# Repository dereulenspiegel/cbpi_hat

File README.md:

# CraftBeerPi Hat
This is a Raspberry Pi hat meant for use with [CraftBeerPi](https://github.com/craftbeerpi/craftbeerpi4).
It's created with [EasyEDA](https://easyeda.com/) and optimized for production via 
[JLCPCB](https://jlcpcb.com/).

This project is [certified](https://certification.oshwa.org/de000132.html) as open source
hardware by the [OSHWA](https://www.oshwa.org/) under the UID DE000132.

## Development

Currently this project is designed with [EasyEDA](https://easyeda.com/). You can find
all necessary files in the folder `easyeda`. When modifying this project please
respect the CERN-OHL-S license used in this project.

## Features

* Slots for up to 5 MAX31865 modules for PT100/PT1000 measurements
* 7 digital outputs with up to 1 amp of output power
* All 7 outputs have flyback diodes to drive inductive loads like solenoids
* All 7 outputs have resettable fuses for extra protection
* RTC so the Raspberry Pi doesn't loose its time in offline installations
* QWIIC connector to hookup additional sensors and actors following the 
  SparkFun QWIIC specification
* OneWire connection for additional sensors
* Can operate on 12-24V, digital outputs operate directly on input voltage
* Reverse voltage protection (but please be still be careful)

Please note that the digital outputs are inverted in logic due to the push pull stage, but
CraftBeerPi supports inverting GPIO actors.

# Polarity of connectors!!!

This board is powered by 12-24V and provides some reverse polarity protection. But still
please be careful when wiring up the board. Looking at the front of a connector the left
side of a connector is always the negative side and the right side of a connector is always
the positive side!

PCB:

Schematic:

## PIN configuration

### Digital outputs

Digital outputs are counted starting on the most left. Outputs 2,3 and 7 are marked on the edge of
the PCBs upper layer. On the bottom layer every output is numbered and the polarity marked. On the
upper layer polarity markings are only next to the outer most ports on each side. But polarity is
always left side negative, right side positive.

| Output # | GPIO |
|----------|------|
| 1 | 25 |
| 2 |  8 |
| 3 |  7 |
| 4 | 12 |
| 5 | 16 |
| 6 | 20 |
| 7 | 21 |

### MAX31865 modules

The MAX31865 modules are connected via SPI and each have a different CS-Pin. Modules
1,2,3,5 are mounted with the upper side facing left (towards the power connector and the SD-card
slot of the Raspberry Pi). Module 5 is flipped 180°. Every module connector has the first two and
last two pins marked with the same markings as the module to ensure the correct orientation.

| Modules # | GPIO CS |
|-----------|---------|
| 1 | 17 |
| 2 | 27 |
| 3 | 22 |
| 4 |  5 |
| 5 |  6 |

### OneWire

The OneWire data line is connected to `GPIO 4`. The pins on the connector are marked behind the connector
on the top side of the PCB. They are, from left to right `VCC` - `DAT` - `GND`. A 4.7k pull up is
already provided on the board.
To enable OneWire support on a Raspberry Pi you need to add
```
dtoverlay=w1-gpio,gpiopin=4
```
to your config.txt

### RealTime Clock

The RTC (DS3231) is connected via I2C and should be usable by adding
```
dtparam=i2c_arm=on
dtoverlay=i2c-rtc,ds3231
```
to your config.txt

## Known Caveats

### Revision 1.0

* On revision 1.0 outputs 2 and 3 are mapped to chip enable pins of SPI0. Users need to disable CE pins on SPI0
* On revision 1.0 outputs are not in the desired off state during and directly after boot

To solve these issues the Raspberry Pi can be configured via config.txt.
With adding `dtoverlay=spi0-0cs` to the config.txt you can disable the hardware CE pins for SPI 0, freeing up GPIO 7 and 8
making Output 2 and 3 freely usabel.
With `gpio=25,7,8,12,16,20,21=op,dh` in the config.txt we set all pins controlling powered outputs to output and pull them high
as early as possible to disable the outputs. During power on there might be less than a second where the outputs might be enabled.

## Full config.txt additions for this board

```
# Enable SPI
dtparam=spi=on
# Enable 1-Wire
dtoverlay=w1-gpio,gpiopin=4
# Enable RTC
dtparam=i2c_arm=on
dtoverlay=i2c-rtc,ds3231
# Disable SPI0 CE pins
dtoverlay=spi0-0cs
# Disable outputs on boot
gpio=25,7,8,12,16,20,21=op,dh
```

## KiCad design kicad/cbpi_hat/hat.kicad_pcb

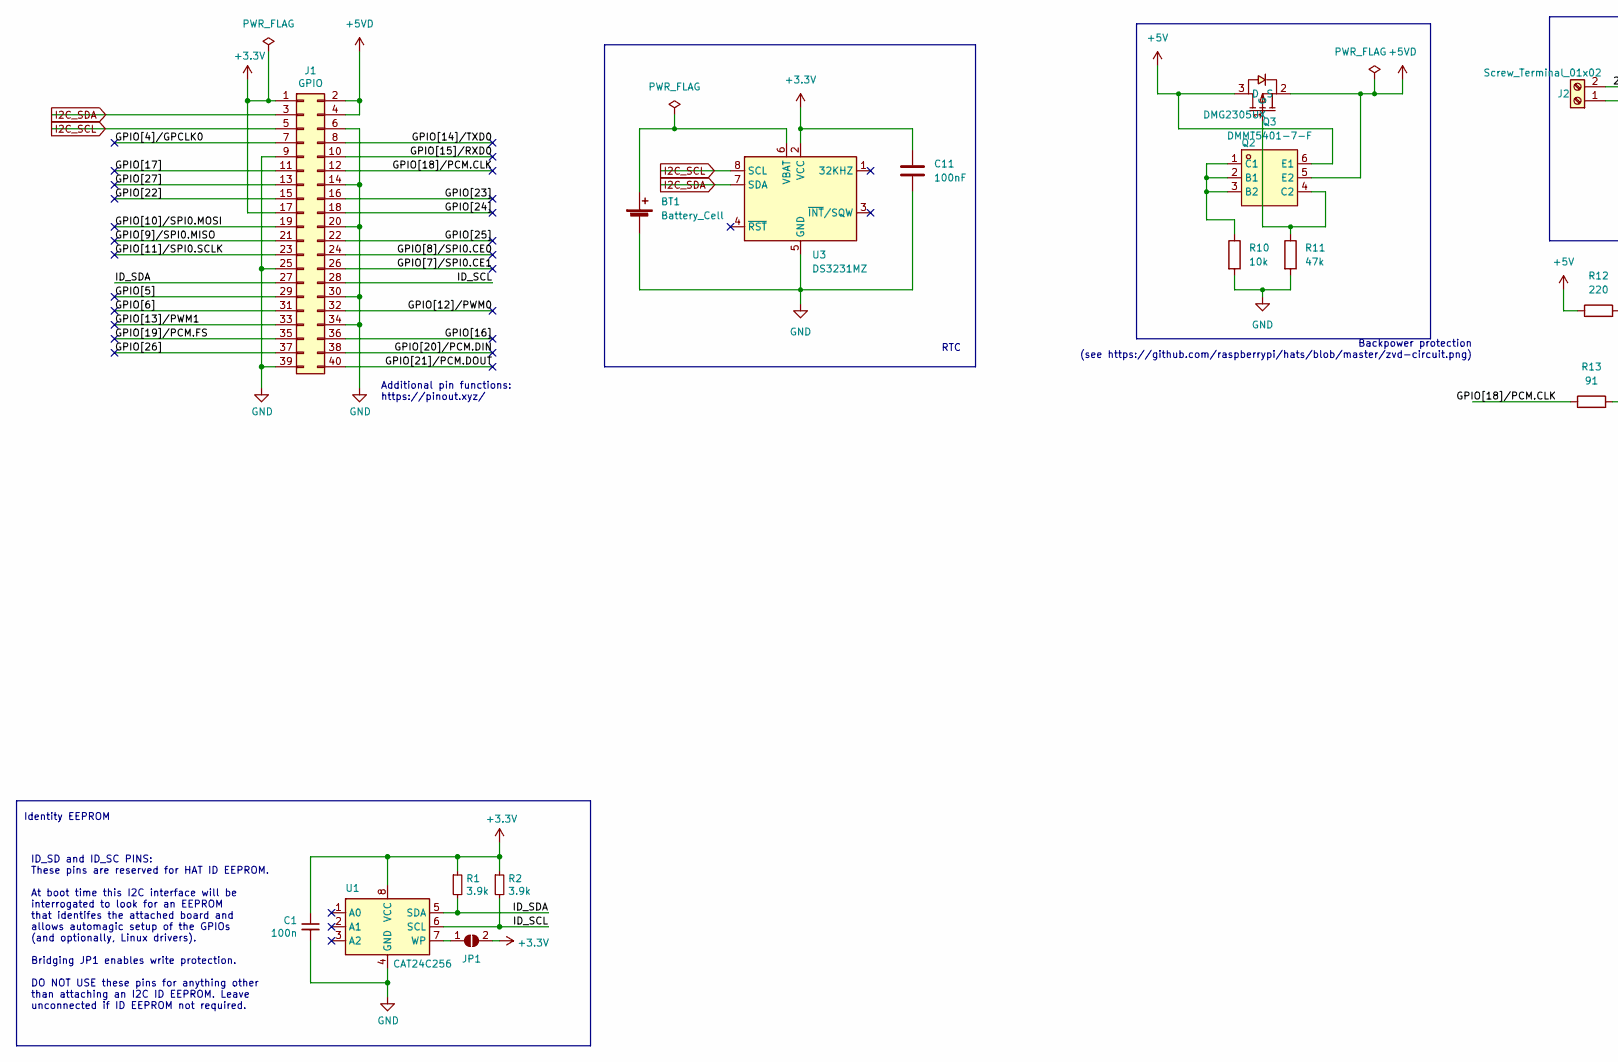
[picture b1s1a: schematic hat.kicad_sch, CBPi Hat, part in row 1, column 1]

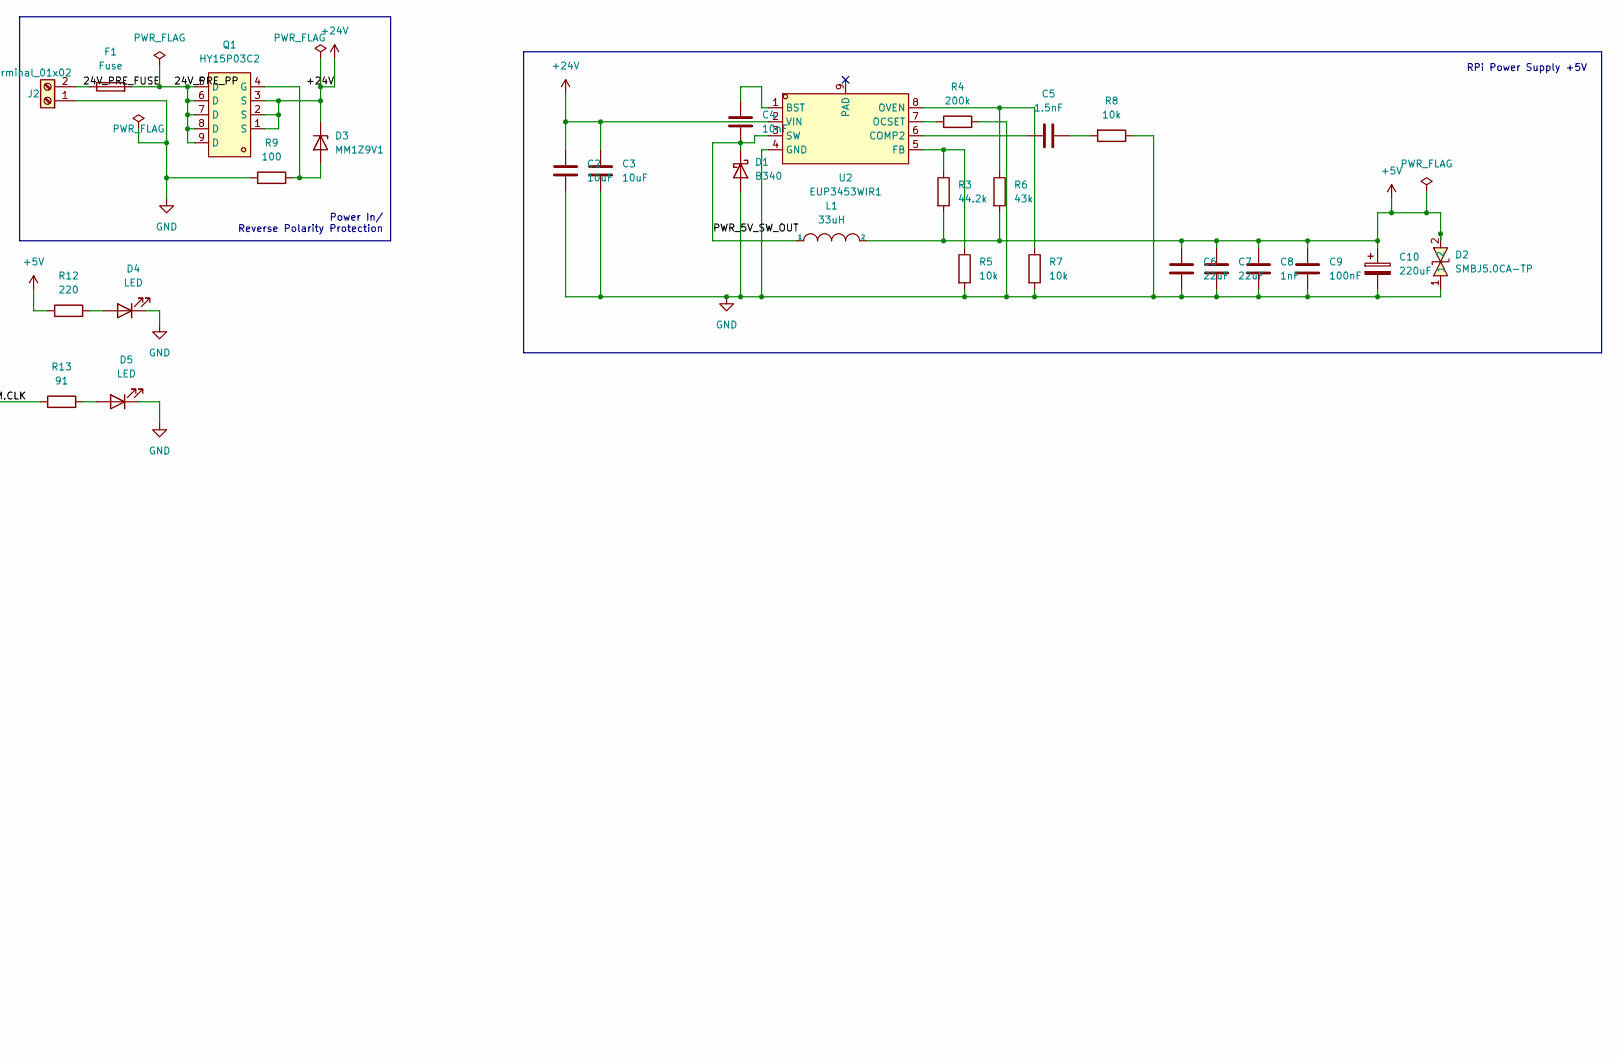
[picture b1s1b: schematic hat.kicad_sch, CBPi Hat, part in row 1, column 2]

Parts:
BT1: Battery_Cell; BAT-TH_CR2032-BS-5-1
C1: 100n; C_0603_1608Metric
C2, C3: 10uF; C_1206_3216Metric
C4: 10nF; C_0603_1608Metric
C5: 1.5nF; C_0603_1608Metric
C6, C7: 22uF; C_0805_2012Metric
C8: 1nF; C_0603_1608Metric
C9, C11: 100nF; C_0603_1608Metric
C10: 220uF; C_Elec_6.3x5.4
D1: B340; D_SMA
D2: SMBJ5.0CA-TP; SMB_L4.6-W3.6-LS5.3-BI; LCSC Part C78757
D3: MM1Z9V1; D_SOD-123
D4, D5: LED; LED_0603_1608Metric
F1: Fuse; Fuse_Blade_ATO_directSolder
J1: GPIO; PinSocket_2x20_P2.54mm_Vertical
J2: Screw_Terminal_01x02; TerminalBlock_Altech_AK300-2_P5.00mm
JP1: ID_WP; SolderJumper-2_P1.3mm_Open_RoundedPad1.0x1.5mm
L1: 33uH; IND-SMD_L11.5-W10.0
Q1: HY15P03C2; DFN-8_L5.9-W5.2-P1.27-LS6.2-BL; LCSC Part C123687
Q2: DMG2305UX; SOT-23-3_L2.9-W1.3-P0.95-LS2.4-BR-1; LCSC Part C2940629
Q3: DMMT5401-7-F; SOT-23-6_L2.9-W1.6-P0.95-LS2.8-BR; LCSC Part C154733
R1, R2: 3.9k; R_0402_1005Metric
R3: 44.2k; R_0402_1005Metric
R4: 200k; R_0402_1005Metric
R5, R7, R8: 10k; R_0603_1608Metric
R6: 43k; R_0603_1608Metric
R9: 100; R_0402_1005Metric
R10: 10k; R_0402_1005Metric
R11: 47k; R_0402_1005Metric
R12: 220; R_0402_1005Metric
R13: 91; R_0402_1005Metric
U1: CAT24C256; SOIC-8-1EP_3.9x4.9mm_P1.27mm_EP2.29x3mm
U2: EUP3453WIR1; SOIC-8_L4.9-W3.9-P1.27-LS6.0-BL-EP3.1; LCSC Part C311687
U3: DS3231MZ; SOIC-8_3.9x4.9mm_P1.27mm

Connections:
+3.3V: C1.1, C11.1, J1.1, J1.17, JP1.2 (B), R1.1, R2.1, U1.8 (VCC), U3.2 (VCC)
+5V: C6.1, C7.1, C8.1, C9.1, C10.1, D2.2, L1.2, Q2.3 (D), Q3.6 (E1), R3.2, R6.2, R12.1
+5VD: J1.2, J1.4, Q2.2 (S), Q3.5 (E2)
+24V: C2.1, C3.1, D3.1 (K), Q1.1 (S), Q1.2 (S), Q1.3 (S), U2.2 (VIN)
/24V_PRE_FUSE: F1.1, J2.2
/24V_PRE_PP: F1.2, Q1.5 (D), Q1.6 (D), Q1.7 (D), Q1.8 (D), Q1.9 (D)
/GPIO[4]/GPCLK0: J1.7
/GPIO[5]: J1.29
/GPIO[6]: J1.31
/GPIO[7]/SPI0.CE1: J1.26
/GPIO[8]/SPI0.CE0: J1.24
/GPIO[9]/SPI0.MISO: J1.21
/GPIO[10]/SPI0.MOSI: J1.19
/GPIO[11]/SPI0.SCLK: J1.23
/GPIO[12]/PWM0: J1.32
/GPIO[13]/PWM1: J1.33
/GPIO[14]/TXD0: J1.8
/GPIO[15]/RXD0: J1.10
/GPIO[16]: J1.36
/GPIO[17]: J1.11
/GPIO[18]/PCM.CLK: J1.12, R13.1
/GPIO[19]/PCM.FS: J1.35
/GPIO[20]/PCM.DIN: J1.38
/GPIO[21]/PCM.DOUT: J1.40
/GPIO[22]: J1.15
/GPIO[23]: J1.16
/GPIO[24]: J1.18
/GPIO[25]: J1.22
/GPIO[26]: J1.37
/GPIO[27]: J1.13
/ID_SCL: J1.28, R2.2, U1.6 (SCL)
/ID_SDA: J1.27, R1.2, U1.5 (SDA)
/PWR_5V_SW_OUT: C4.2, D1.1 (K), L1.1, U2.3 (SW)
GND: BT1.2 (-), C1.2, C2.2, C3.2, C6.2, C7.2, C8.2, C9.2, C10.2, C11.2, D1.2 (A), D2.1, D4.1 (K), D5.1 (K), J1.6, J1.9, J1.14, J1.20, J1.25, J1.30, J1.34, J1.39, J2.1, R4.2, R5.2, R7.2, R8.1, R9.1, R10.2, R11.2, U1.4 (GND), U2.4 (GND), U3.5 (GND)
I2C_SCL: J1.5, U3.8 (SCL)
I2C_SDA: J1.3, U3.7 (SDA)
unnamed: BT1.1 (+), U3.6 (VBAT)
unnamed: C4.1, U2.1 (BST)
unnamed: C5.1, U2.6 (COMP2)
unnamed: C5.2, R8.2
unnamed: D3.2 (A), Q1.4 (G), R9.2
unnamed: D4.2 (A), R12.2
unnamed: D5.2 (A), R13.2
unnamed: JP1.1 (A), U1.7 (WP)
unnamed: Q2.1 (G), Q3.4 (C2), R11.1
unnamed: Q3.1 (C1), Q3.2 (B1), Q3.3 (B2), R10.1
unnamed: R3.1, R5.1, U2.5 (FB)
unnamed: R4.1, U2.7 (OCSET)
unnamed: R6.1, R7.1, U2.8 (OVEN)

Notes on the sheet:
Additional pin functions: https://pinout.xyz/
Identity EEPROM
ID_SD and ID_SC PINS: These pins are reserved for HAT ID EEPROM. At boot time this I2C interface will be interrogated to look for an EEPROM that identifes the attached board and allows automagic setup of the GPIOs (and optionally, Linux drivers). Bridging JP1 enables write protection. DO NOT USE th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
RTC
Backpower protection (see https://github.com/raspberrypi/hats/blob/master/zvd-circuit.png)
RPi Power Supply +5V
Power In/ Reverse Polarity Protection

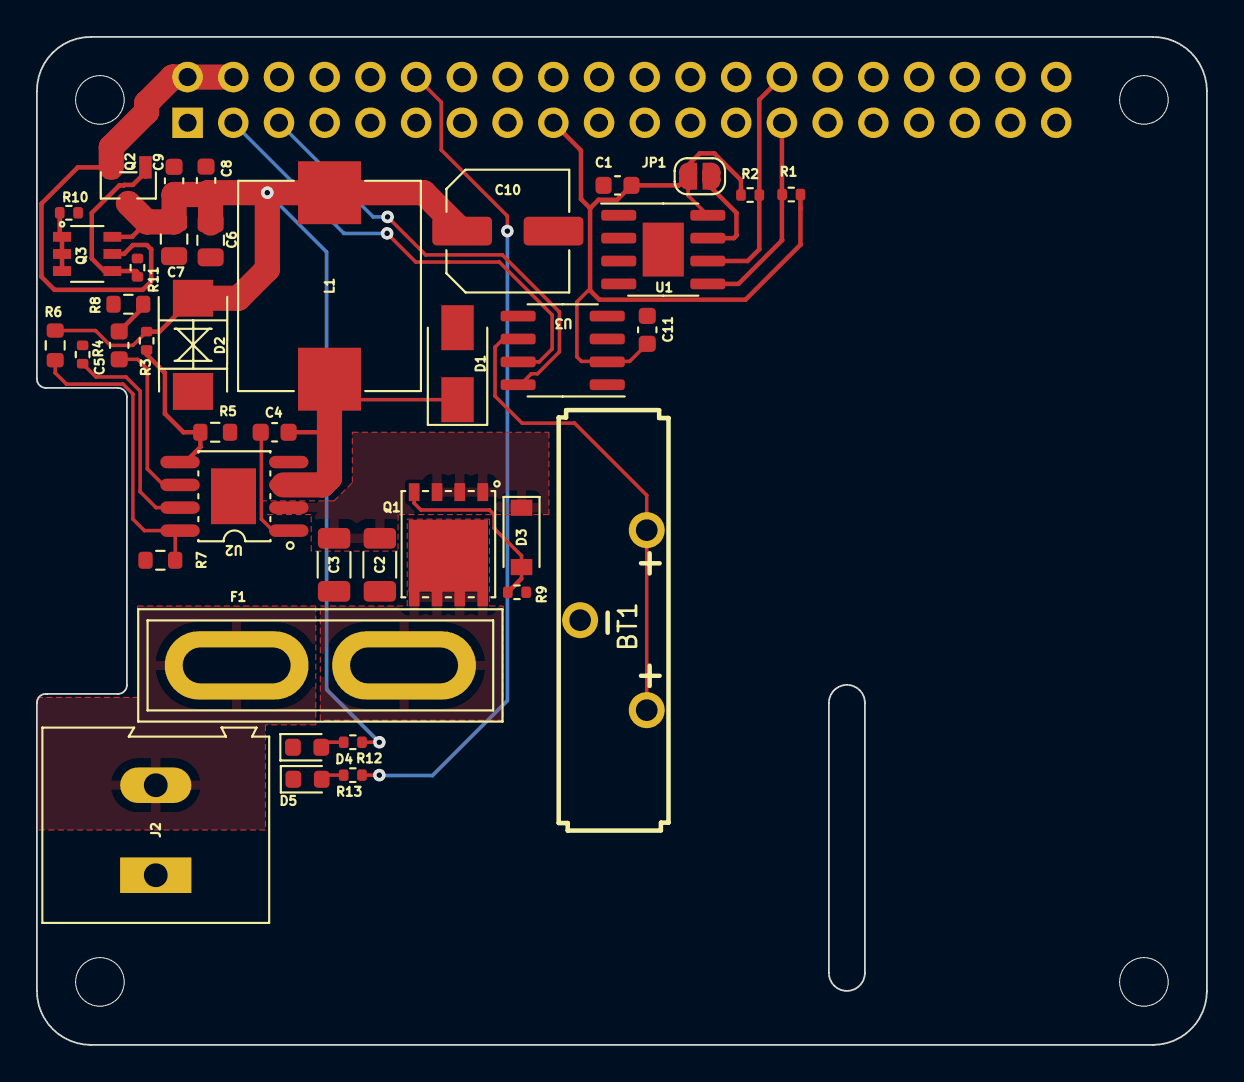
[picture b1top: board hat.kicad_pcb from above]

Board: 2 copper layers, 65.0 x 56.0 mm, 45 parts (1 on the bottom side), 26 nets.

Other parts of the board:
MH1, MH2, MH3, MH4: MountingHole_2.7mm_M2.5

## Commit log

2023-01-02 “root”
2023-01-02 Added image of schematic
2023-01-02 Added exports of production files
2023-01-02 Added pin documentation
2023-01-03 minor upgrades, mostly regarding text and documentation on the board. Improved resistors on MOSFET gates, so they don't form an unnecessary voltage divider
2023-01-03 Updated exported pictures after board changes
2023-01-03 Updated EasyEDA exports after board changes
2023-01-09 Rather large change on the PCB introducing fuses on each output and a push pull schematic for more protection of the raspberry pi as well as pull up resistors to have a defined off state for every ou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
2023-01-10 Board has now better protection in the 5V supply for the Raspberry Pi and a few optimizations and corrections in the silscreen layers and part placement
2023-01-10 Added LTSpice circuit of the digital output to simulate and verify its behavior
2023-01-10 Added note to warn users, that the digital ouputs are inverted in logic
2023-01-11 Added power indicator LED to 5V rail and further optimized a few parts placements
2023-01-11 Accidentally pushed the wrong image image as pcb image
2023-01-11 Again a few minor changes in parts placement. Mostly to optimize readability of upper silkscreen
2023-01-12 Optimized parts placement further and added reverse polarity protection, which hopefully works
2023-01-12 Fixed typos in README
2023-01-12 Added reverse volatege protection as a feature
2023-01-12 Optimized parts placement for better ground planes, as we will pump up to 10 amps through this board
2023-01-12 Fixed typo
2023-01-13 More optimization on pcb traces running power, to minimize losses towards the Pi and possibly power hungry 1 wire devices
2023-01-13 Added missing capacitator to VCC on DS3231
2023-01-13 Added documentation how to enable OneWire support on a Raspberry Pi
2023-01-13 Added top layer markings to easier identify the board
2023-01-13 Moved upper side markings, as I placed them accidentally above a cutout
2023-01-13 Added missing capacitator
2023-01-15 A few more optimizations in parts and trace placement
2023-01-17 Added CERN-OHL-S as intended license for this hardware design
2023-01-17 Added section about development to make it more obvious how to modify and contribute to this project
2023-01-17 The MOSFETs gates on the outputs are now controlled by 5V instead of 3.3V which should lower the internal resistance of the MOSFETs and give us more safety margin
2023-01-19 Added newly received OSHWA certification
2023-02-03 Added know caveats for revision 1.0 to README
2023-02-04 Added description for adding necessary lines to config.txt
2023-02-04 Added first documentation in the form of a mdbook. To be continued
2023-02-05 Added workflow to render our documentation
2023-02-05 Added diagrams explaining the hardware functions
2023-02-05 deploy: e717b4986addfc37ae34926a5bb16fdf241720e7
2023-02-05 Forgot that applefs is now case sensitive by default, but the fs on the github runner is
2023-02-05 deploy: 61404a68b57c839c8c5450896d701ce60ec921d9
2023-02-05 Trying to fix the intro site
2023-02-05 deploy: 5516a82cfa91702a52ddab9a7446b4a196d6409d
2023-02-05 Fixed typos
2023-02-11 Added empty kicad project
2023-02-11 Added EUP3453 dc dc converter to project library
2023-02-11 Reimplemented the 5V power supply for the Raspberry Pi in KiCAD
2023-02-11 Added smbj5.0 over voltage protection to project library
2023-02-11 KiCAD wanted to save more changes
2023-02-13 Updated symbol library with project relative path
2023-02-13 Restarted the KiCAD design based on the official Hat template
2023-02-13 Added footprints etc. for the 33uH inductance
2023-02-13 Assigned all footprints to the DC DC converter
2023-02-15 Added gitignore so we don't checkin the kicad backups anymore
2023-02-15 Upadted pin definitions of library symbols to get rid of erc warnings
2023-02-15 We now have no erc errors or warnings for now
2023-02-15 Added library for mosfet for the reverse polarity protection
2023-02-15 The schematic should now have the current reverse polarity proection
2023-02-15 Placed first components on board, no routing yet
2023-02-18 5V DC-DC converter is largely routed including reverse polarity protection
2023-02-18 Added protection against back powering. This should fix #12
2023-02-18 DC-DC converter and identity eeprom should be fully routed now (except for GND).
2023-02-18 RTC is now in the schematic
2023-02-18 RTC block is now annotated
2023-02-18 Started to divide the documentation so we can introduce and document the next revision more easily
2023-02-18 Added RTC to board
2023-02-18 Added power and warning LED. This should address #13 and fix it
2023-02-19 Replaced CR2032 holder with the old more space saving one and fixed all DRC errors and warnings except for unconnected GND
